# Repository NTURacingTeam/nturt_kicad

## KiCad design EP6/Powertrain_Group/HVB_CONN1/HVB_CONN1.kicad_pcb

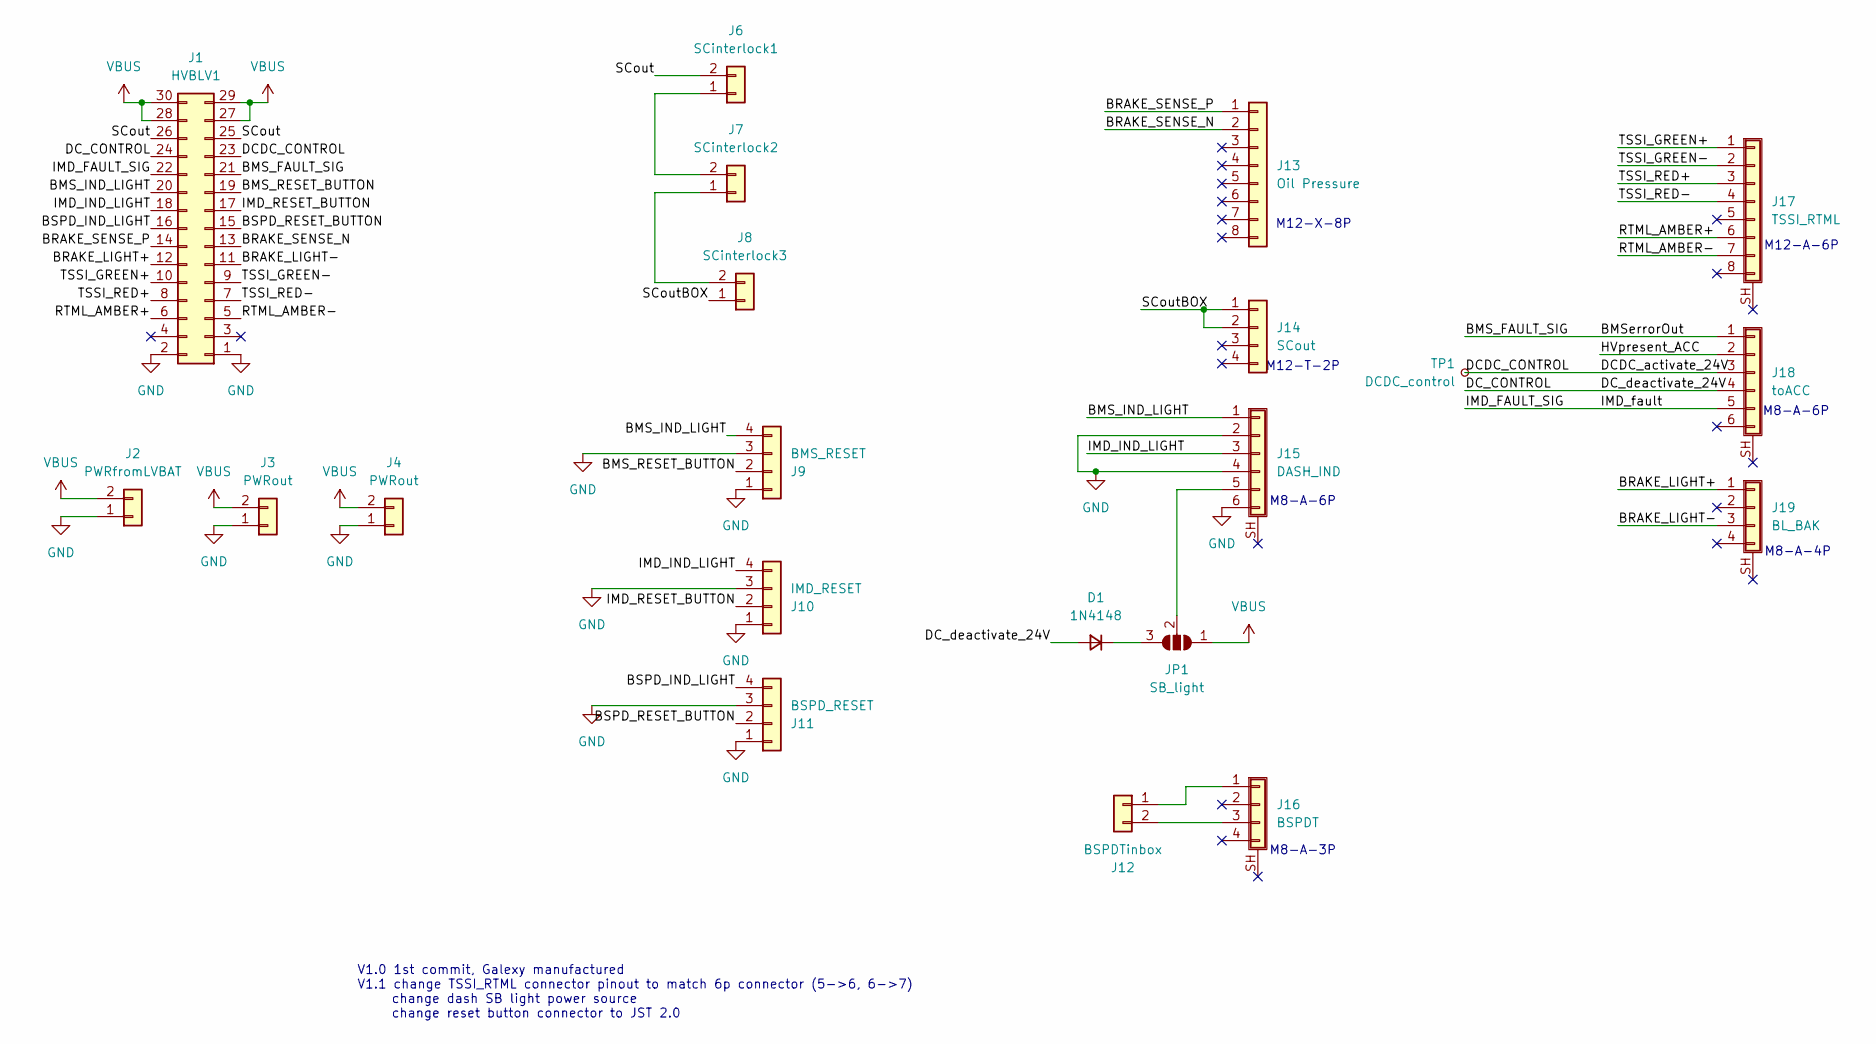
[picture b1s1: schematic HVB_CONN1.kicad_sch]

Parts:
D1: 1N4148; D_SOD-323_HandSoldering
J1: HVBLV1; IDC-Header_2x15_P2.54mm_Vertical_SMD
J2: PWRfromLVBAT; JST_VH_B2P-VH_1x02_P3.96mm_Vertical
J3, J4: PWRout; JST_VH_B2P-VH_1x02_P3.96mm_Vertical
J6: SCinterlock1; JST_VH_B2P-VH_1x02_P3.96mm_Vertical
J7: SCinterlock2; JST_VH_B2P-VH_1x02_P3.96mm_Vertical
J8: SCinterlock3; JST_VH_B2P-VH_1x02_P3.96mm_Vertical
J9: BMS_RESET; JST_PH_B4B-PH-K_1x04_P2.00mm_Vertical
J10: IMD_RESET; JST_PH_B4B-PH-K_1x04_P2.00mm_Vertical
J11: BSPD_RESET; JST_PH_B4B-PH-K_1x04_P2.00mm_Vertical
J12: BSPDTinbox; JST_PH_B2B-PH-K_1x02_P2.00mm_Vertical
J13: Oil Pressure; NianYeong-M12-X-F4P
J14: SCout; NianYeong-M12-T-M4P
J15: DASH_IND; WP-06F3-09-11
J16: BSPDT; WP-03F3-09-11
J17: TSSI_RTML; NianYeong-M12-A-F8P-Shield
J18: toACC; WP-06F3-09-11
J19: BL_BAK; WP-04F3-26-11
JP1: SB_light; SolderJumper-3_P1.3mm_Open_RoundedPad1.0x1.5mm
TP1: DCDC_control; TestPoint_Pad_D1.0mm

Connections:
/BMS_FAULT_SIG: J1.21, J18.1
/BMS_IND_LIGHT: J1.20, J9.4, J15.1
/BMS_RESET_BUTTON: J1.19, J9.2
/BRAKE_LIGHT+: J1.12, J19.1
/BRAKE_LIGHT-: J1.11, J19.3
/BRAKE_SENSE_N: J1.13, J13.2
/BRAKE_SENSE_P: J1.14, J13.1
/BSPD_IND_LIGHT: J1.16, J11.4
/BSPD_RESET_BUTTON: J1.15, J11.2
/DCDC_CONTROL: J1.23, J18.3, TP1.1
/DC_CONTROL: D1.2 (A), J1.24, J18.4
/HVpresent_ACC: J18.2
/IMD_FAULT_SIG: J1.22, J18.5
/IMD_IND_LIGHT: J1.18, J10.4, J15.3
/IMD_RESET_BUTTON: J1.17, J10.2
/RTML_AMBER+: J1.6, J17.6
/RTML_AMBER-: J1.5, J17.7
/SCout: J1.25, J1.26, J6.2
/SCoutBOX: J8.1, J14.1, J14.2
/TSSI_GREEN+: J1.10, J17.1
/TSSI_GREEN-: J1.9, J17.2
/TSSI_RED+: J1.8, J17.3
/TSSI_RED-: J1.7, J17.4
GND: J1.1, J1.2, J2.1, J3.1, J4.1, J9.1, J9.3, J10.1, J10.3, J11.1, J11.3, J15.2, J15.4, J15.6
unnamed: D1.1 (K), JP1.3 (B)
unnamed: J6.1, J7.2
unnamed: J7.1, J8.2
unnamed: J12.1, J16.1
unnamed: J12.2, J16.3
unnamed: J15.5, JP1.2 (C)
VBUS: J1.27, J1.28, J1.29, J1.30, J2.2, J3.2, J4.2, JP1.1 (A)

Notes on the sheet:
M12-T-2P
M8-A-4P
M12-X-8P
M8-A-3P
M12-A-6P
V1.0 1st commit, Galexy manufactured V1.1 change TSSI_RTML connector pinout to match 6p connector (5->6, 6->7) change dash SB light power source change reset button connector to JST 2.0
M8-A-6P

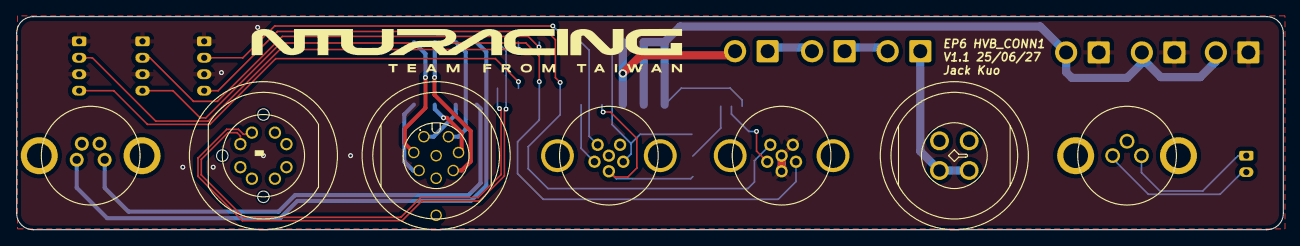
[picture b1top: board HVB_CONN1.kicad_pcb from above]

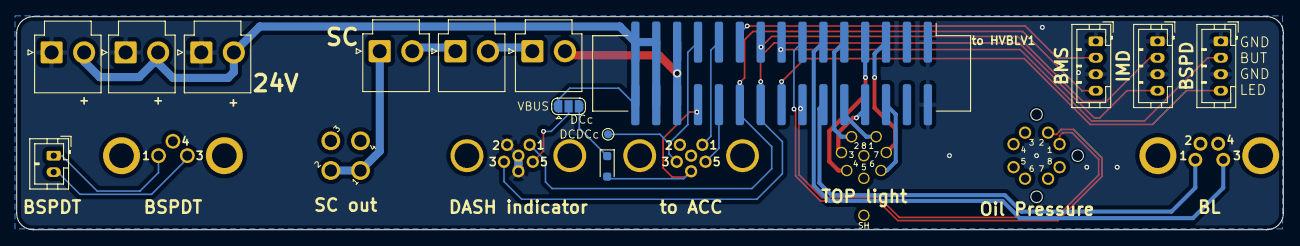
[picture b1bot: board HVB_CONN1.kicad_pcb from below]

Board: 2 copper layers, 154.0 x 25.9 mm, 21 parts (14 on the bottom side), 30 nets.

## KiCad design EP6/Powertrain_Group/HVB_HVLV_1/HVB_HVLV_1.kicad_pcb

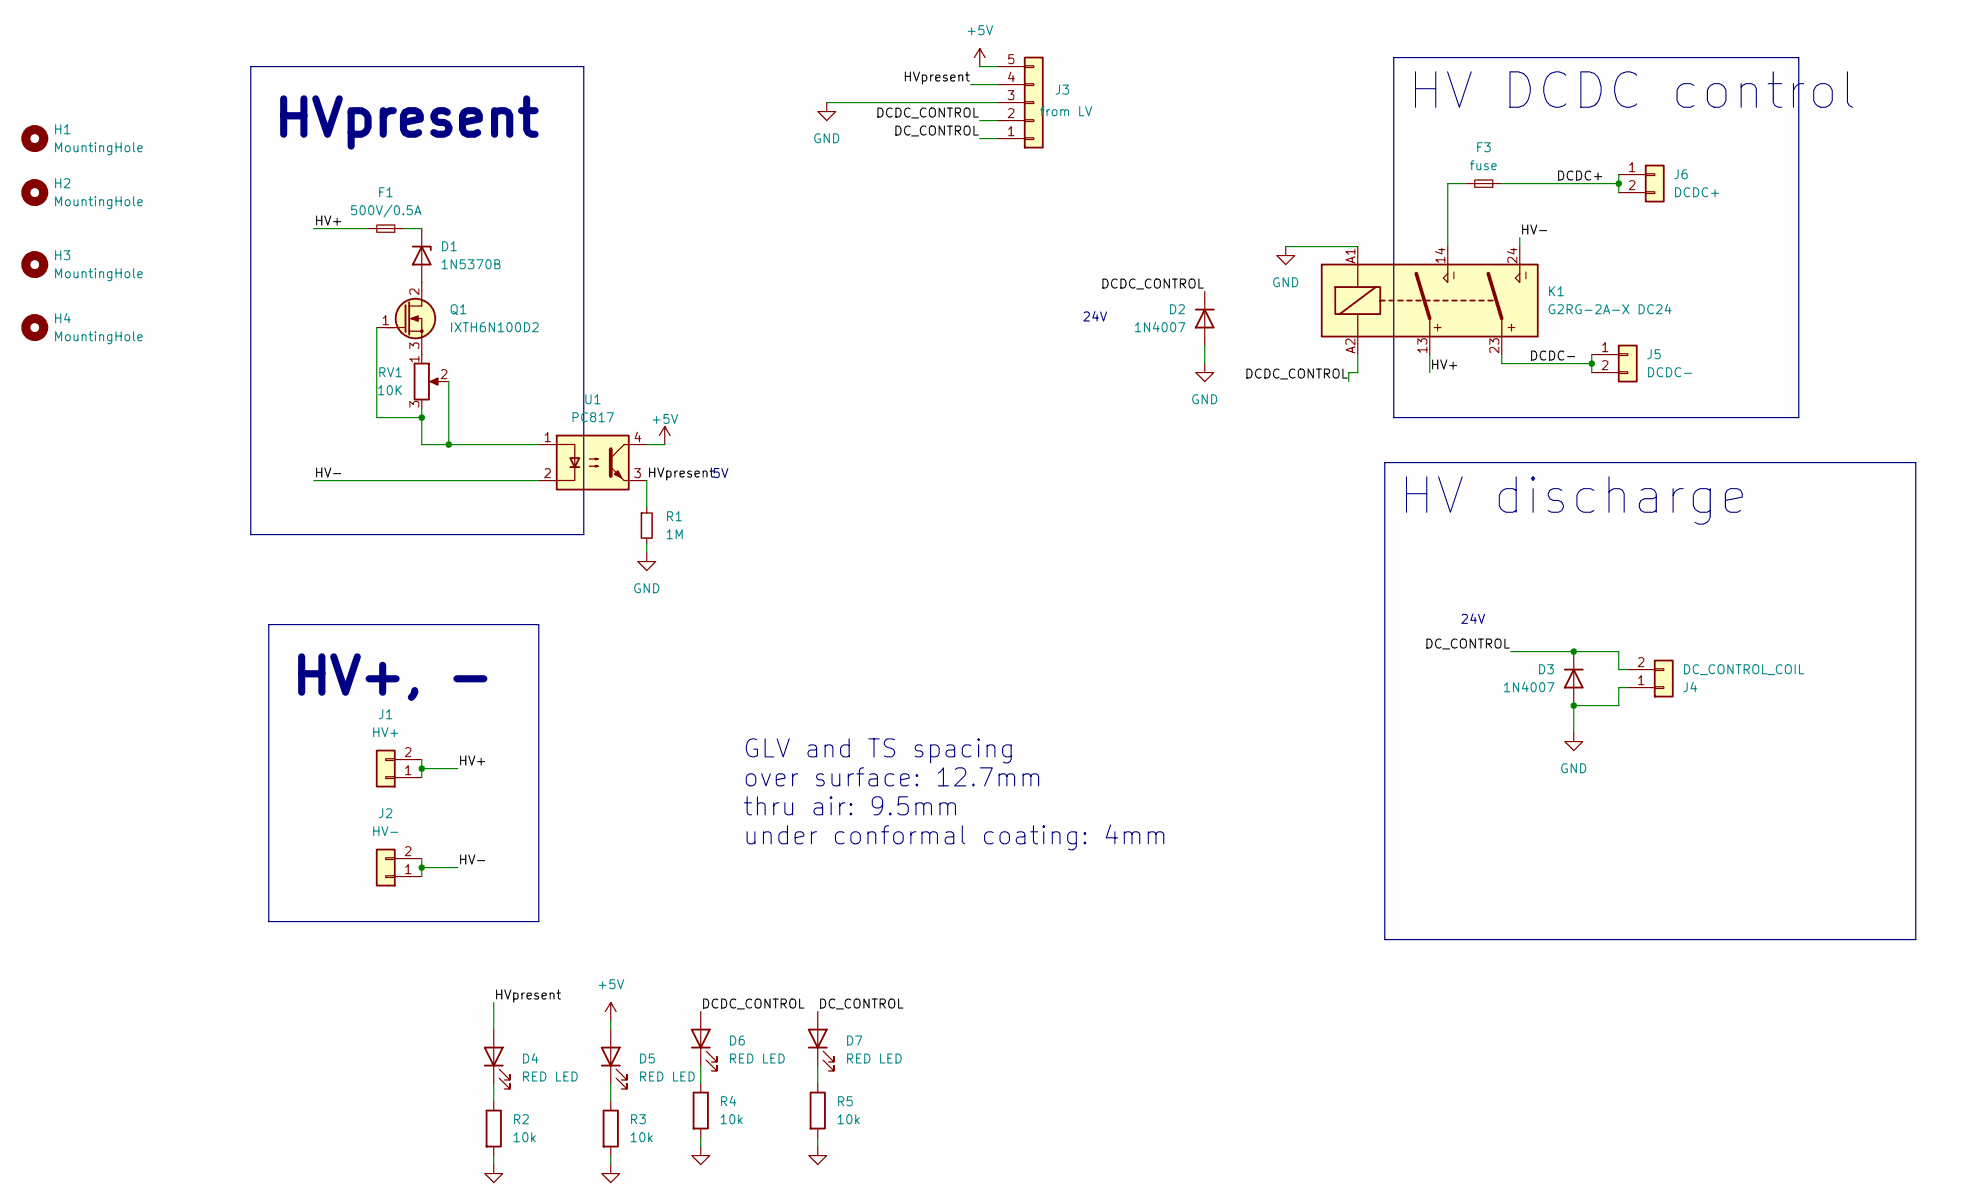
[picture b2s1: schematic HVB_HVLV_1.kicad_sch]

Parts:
D1: 1N5370B; D_DO-201_P15.24mm_Horizontal
D2, D3: 1N4007; D_DO-41_SOD81_P10.16mm_Horizontal
D4, D5, D6, D7: RED LED; LED_0603_1608Metric
F1: 500V/0.5A; 65600001009; Rating W
F3: fuse; 65600001009; Rating W
H1, H2, H3, H4: MountingHole; MountingHole_3.2mm_M3
J1: HV+; HRS_DF33C-2P-3.3DSA
J2: HV-; HRS_DF33C-2P-3.3DSA
J3: from LV; JST_PH_B5B-PH-K_1x05_P2.00mm_Vertical
J4: DC_CONTROL_COIL; JST_VH_B2P-VH_1x02_P3.96mm_Vertical
J5: DCDC-; HRS_DF33C-2P-3.3DSA
J6: DCDC+; HRS_DF33C-2P-3.3DSA
K1: G2RG-2A-X DC24; Relay_DPST_Omron_G2RL-2A
Q1: IXTH6N100D2; TO-247-3_Vertical_GDS
R1: 1M; R_0603_1608Metric
R2, R3, R4, R5: 10k; R_0603_1608Metric
RV1: 10K; Throughhole Potentiometer 3296W
U1: PC817; DIP-4_W7.62mm

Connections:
+5V: D5.2 (A), J3.5, U1.4
/DCDC+: F3.1, J6.1, J6.2
/DCDC-: J5.1, J5.2, K1.23
/DCDC_CONTROL: D2.1 (K), D6.2 (A), J3.2, K1.A2
/DC_CONTROL: D3.1 (K), D7.2 (A), J3.1, J4.2
/HV+: F1.2, J1.1, J1.2, K1.13
/HV-: J2.1, J2.2, K1.24, U1.2
/HVpresent: D4.2 (A), J3.4, R1.1, U1.3
GND: D2.2 (A), D3.2 (A), J3.3, J4.1, K1.A1, R1.2, R2.2, R3.2, R4.2, R5.2
unnamed: D1.2 (A), Q1.2 (D)
unnamed: D1.1 (K), F1.1
unnamed: D4.1 (K), R2.1
unnamed: D5.1 (K), R3.1
unnamed: D6.1 (K), R4.1
unnamed: D7.1 (K), R5.1
unnamed: F3.2, K1.14
unnamed: Q1.1 (G), RV1.2, RV1.3, U1.1
unnamed: Q1.3 (S), RV1.1

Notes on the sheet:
HVpresent
HV DCDC control
24V
HV discharge
HV+, -
GLV and TS spacing over surface: 12.7mm thru air: 9.5mm under conformal coating: 4mm

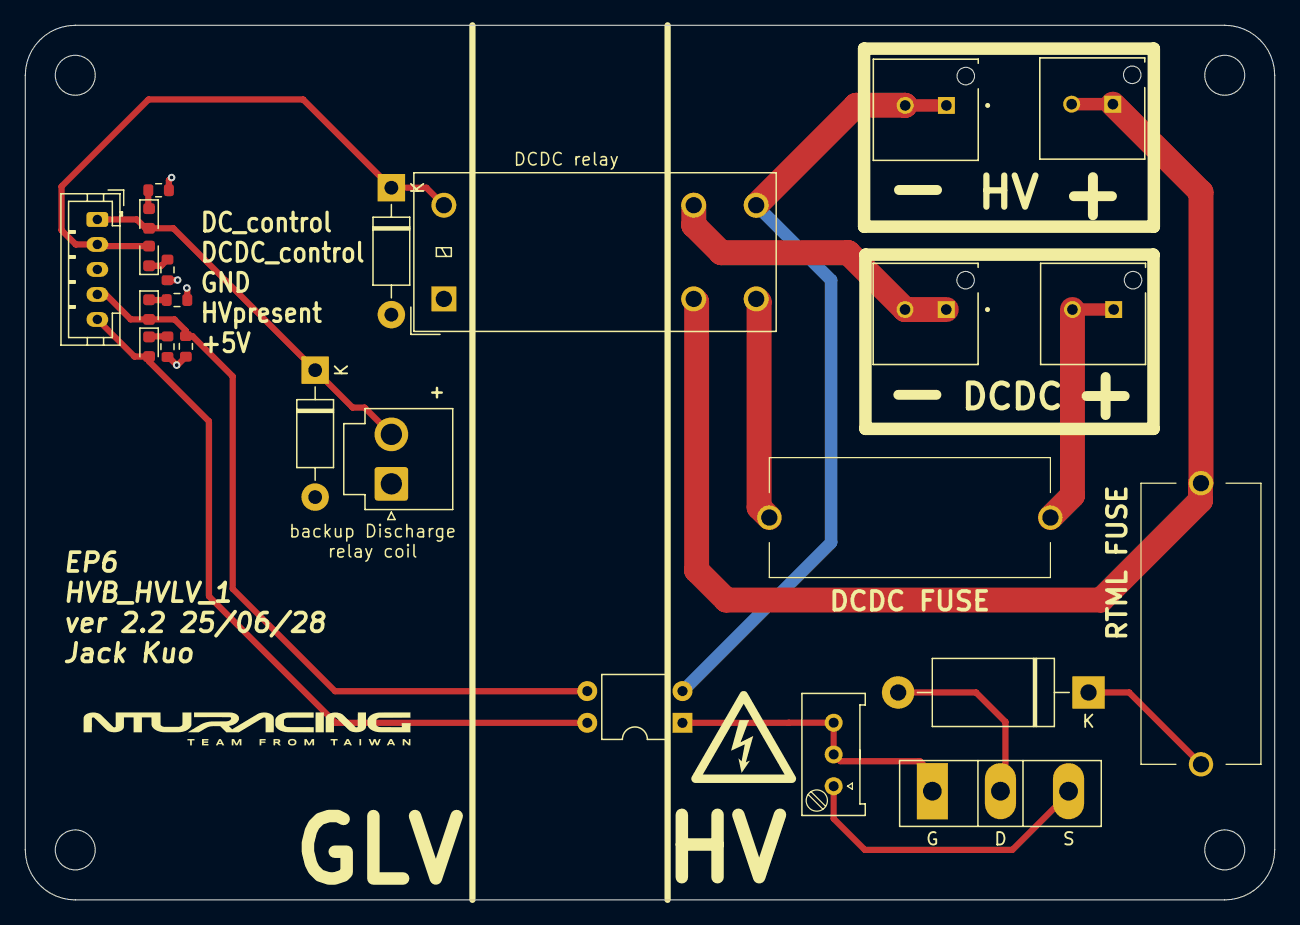
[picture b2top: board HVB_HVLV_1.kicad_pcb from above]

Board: 2 copper layers, 100.0 x 70.0 mm, 28 parts (0 on the bottom side), 18 nets.

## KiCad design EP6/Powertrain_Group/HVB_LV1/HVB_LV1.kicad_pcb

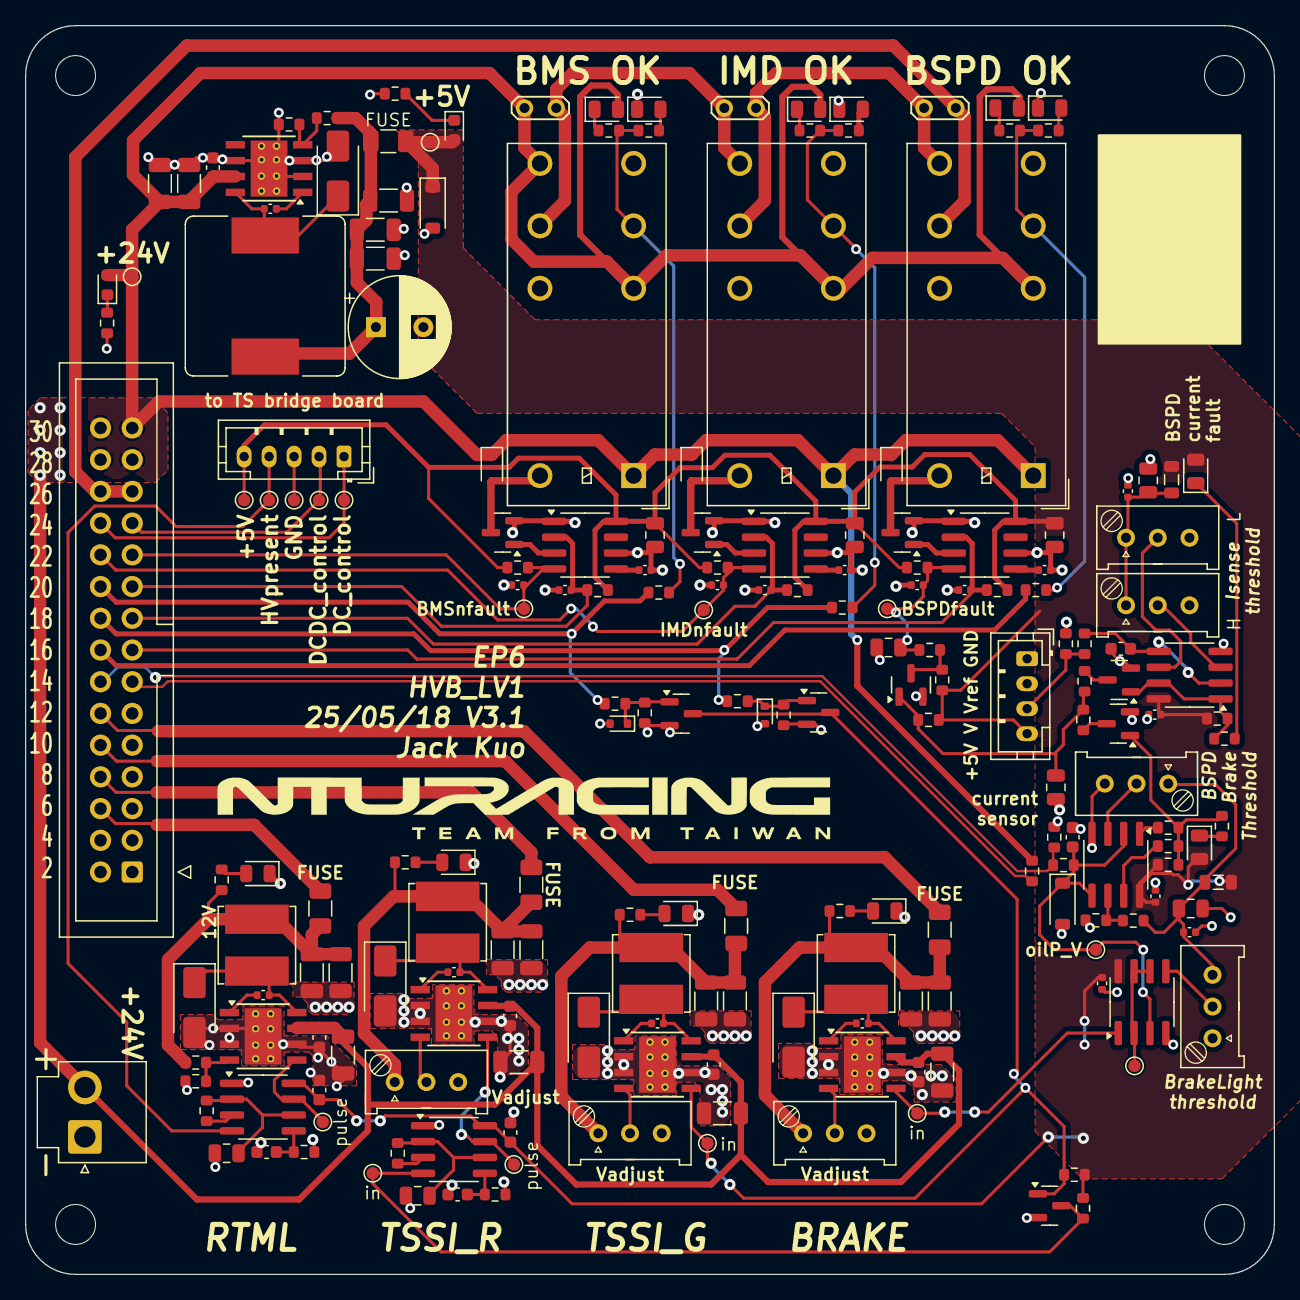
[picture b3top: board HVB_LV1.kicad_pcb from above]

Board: 2 copper layers, 100.0 x 100.0 mm, 208 parts (0 on the bottom side), 102 nets.

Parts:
C1, C5, C9, C14, C17, C19, C52, C55, C57: 10u; C_0805_2012Metric
C2, C4, C6, C8, C10, C12, C13, C15, C16, C20, C21: 100n; C_0402_1005Metric
C3, C7, C11, C22, C30, C35, C40, C45: 10n; C_0402_1005Metric
C18, C56: 10u; C_0603_1608Metric
C23, C24, C31, C36, C41, C46: 10u 35V; C_1206_3216Metric
C25, C32, C37, C42, C47, C50, C51, C53, C54: 100n; C_0603_1608Metric
C26, C27, C28, C33, C34, C38, C39, C43, C44, C48, C49: 22u 25V; C_1206_3216Metric
C29: 330u 25V; CP_Radial_D8.0mm_P3.80mm
D1, D4, D7: 4148; D_SOD-323
D2, D5, D8, D10, D12: GREEN LED; LED_0805_2012Metric
D3, D6, D9: RED LED; LED_0805_2012Metric
D11, D16: 5.6V (C19077402); D_SOD-123
D13, D15: WHITE LED; LED_0603_1608Metric
D14, D19, D20, D21, D22: SS54; D_SMA
D17, D18: BZX584C5V6; D_SOD-523
D23, D24, D25, D26: YELLOW LED; LED_0805_2012Metric
F1: 2A; Fuse_1206_3216Metric
F2, F3, F4, F5: FUSE; Fuse_1206_3216Metric
FB1, FB2: GZ1608D601TF; L_0805_2012Metric
H1, H2, H3, H4: MountingHole; MountingHole_3.2mm_M3
J1: toTS; JST_PH_B5B-PH-K_1x05_P2.00mm_Vertical
J2: energy meter; JST_VH_B2P-VH-B_1x02_P3.96mm_Vertical
J3: toConnectorBoard; IDC-Header_2x15_P2.54mm_Vertical
J4: I_Sen; JST_PH_B4B-PH-K_1x04_P2.00mm_Vertical
JP2, JP3, JP4: test; TestPoint_2Pads_Pitch2.54mm_Drill0.8mm
L1: 22uH 4.95A (SMDRI129-220MT); L_Bourns_SRR1260
L2, L3, L4, L5: 47u 1.6A (SRN6045TA-470M); L_Bourns_SRN6045TA
Q1, Q2, Q3, Q4, Q5, Q6, Q7, Q8, Q9: 2N7002; SOT-23
R1, R2, R5, R6, R7, R10, R11, R12, R15, R21, R25, R35, R37, R38, R39, R41, R44, R46, R48, R50, R51, R52, R53: 10k; R_0603_1608Metric
R3, R8, R13, R18, R19, R27, R29: 0R; R_0603_1608Metric
R4, R9, R14, R23, R31, R32, R40, R42: 100k; R_0603_1608Metric
R16, R17: 10R; R_0603_1608Metric
R20: 150R; R_0603_1608Metric
R22, R30: 4k7; R_0603_1608Metric
R24, R49: 1k; R_0603_1608Metric
R26: 20k; R_0603_1608Metric
R28: 100R; R_0603_1608Metric
R33, R34: 47k; R_0603_1608Metric
R36: 15k; R_0603_1608Metric
R43: 91k; R_0603_1608Metric
R45, R47: 43k; R_0603_1608Metric
RL1, RL2, RL3: G2RL-24-DC24; Relay_DPDT_Omron_G2RL-2
RV1, RV2, RV3, RV4, RV5, RV6, RV7: 10k; Throughhole Potentiometer 3296W
TP1: +5V; TestPoint_Pad_D1.0mm
TP2: HVpresent; TestPoint_Pad_D1.0mm
TP3: GND; TestPoint_Pad_D1.0mm
TP4: DCDC_control; TestPoint_Pad_D1.0mm
TP5: DC_control; TestPoint_Pad_D1.0mm
TP6: BMSfault; TestPoint_Pad_D1.0mm
TP7: IMDfault; TestPoint_Pad_D1.0mm
TP8: BSPDnfault; TestPoint_Pad_D1.0mm
TP9: BrakeThreshold; TestPoint_Pad_D1.0mm
TP10: oilP_Vout; TestPoint_Pad_D1.0mm
TP11: Vbus; TestPoint_Pad_D1.0mm
TP12: 5V; TestPoint_Pad_D1.0mm
TP13: RTML; TestPoint_Pad_D1.0mm
TP14: TSSI RED RAW; TestPoint_Pad_D1.0mm
TP15: TSSI Red; TestPoint_Pad_D1.0mm
TP16: TSSI Green; TestPoint_Pad_D1.0mm
TP17: BrakeLight; TestPoint_Pad_D1.0mm
U1, U2, U3, U12, U13: NE555D; SOIC-8_3.9x4.9mm_P1.27mm
U4: LM358; SOIC-8_3.9x4.9mm_P1.27mm
U5, U6: LM393; SOIC-8_3.9x4.9mm_P1.27mm
U7, U8, U9, U10, U11: TPS5430DDAR; TI_SO-PowerPAD-8_ThermalVias

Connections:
+5V: C1.1, C5.1, C9.1, C15.1, C20.1, C21.1, C50.1, C53.1, D10.2 (A), D12.2 (A), D15.2 (A), D16.1 (K), F1.2, FB1.2, FB2.2, J1.5, J4.4, R1.1, R4.1, R6.1, R9.1, R11.1, R14.1, R21.1, R23.1, R25.1, R31.1, R37.1, R38.1, TP1.1, TP12.1, U1.8 (VCC), U2.8 (VCC), U3.8 (VCC), U4.8 (V+), U5.8 (V+), U6.8 (V+), U12.8 (VCC), U13.8 (VCC)
+5VA: C13.1, C14.1, FB1.1, RV3.1, RV4.1
/BMS_IND_LIGHT: J3.20, R3.2, R39.1
/BMS_RESET_BUTTON: C2.1, J3.19, R1.2, U1.2 (TR)
/BMS_nFAULT_SIG_RAW: C4.1, J3.21, R4.2, TP6.1, U1.4 (R)
/BRAKE_LIGHT+: F5.2, J3.12
/BRAKE_SENSE_N: J3.13, R16.1
/BRAKE_SENSE_P: J3.14, R17.1, R20.1
/BSPD/5VA2: C16.1, C17.1, FB2.1, R26.1, RV1.3, RV2.1
/BSPD/BSPDfault: C57.1, Q5.1 (G), R19.2, R25.2, R29.2
/BSPD/DCbusCurrentAbsent: Q6.1 (G), R30.2, R31.2, U6.1, U6.7
/BSPD/DCbusCurrentNotGood: Q6.3 (D), R29.1
/BSPD/OilPsenserPresent: R27.1, U5.7
/BSPD/brakeLightOn: TP17.1, U4.1, U11.5 (EN)
/BSPD/brakeNotInSafeArea: Q4.3 (D), R19.1
/BSPD/nohardBrake: R18.1, U5.1
/BSPD_IND_LIGHT: J3.16, R13.2
/BSPD_RESET_BUTTON: C10.1, J3.15, R11.2, U3.2 (TR)
/BSPD_nFAULT_SIG: C12.1, C19.1, R14.2, R24.1, TP8.1, U3.4 (R)
/BrightLight/RTML amber/12V_buck: C33.1, C34.1, F2.1, L2.1, R43.1, R50.2
/BrightLight/RTML amber/12V_buck_FB: R43.2, R44.1, U8.4 (VSENSE)
/BrightLight/RTML amber/12V_buck_sw: C30.2, D19.1 (K), L2.2, U8.8 (PH)
/BrightLight/RTML amber/enable: TP13.1, U8.5 (EN), U12.7 (DIS)
/BrightLight/TSSI green/buck_FB: RV6.2, U10.4 (VSENSE)
/BrightLight/TSSI green/buck_out: C43.1, C44.1, F4.1, L4.1, R52.2, RV6.1
/BrightLight/TSSI green/buck_sw: C40.2, D21.1 (K), L4.2, U10.8 (PH)
/BrightLight/TSSI green/enable: Q7.1 (G), Q8.3 (D), Q9.3 (D), R38.2, TP16.1, U10.5 (EN)
/BrightLight/TSSI red pulse/OpenDrain_pulse_out: TP15.1, U9.5 (EN), U13.7 (DIS)
/BrightLight/TSSI red pulse/enable: Q7.3 (D), R37.2, TP14.1, U13.4 (R)
/BrightLight/TSSI red/buck_FB: RV5.2, U9.4 (VSENSE)
/BrightLight/TSSI red/buck_out: C38.1, C39.1, F3.1, L3.1, R51.2, RV5.1
/BrightLight/TSSI red/buck_sw: C35.2, D20.1 (K), L3.2, U9.8 (PH)
/BrightLight/brakelight/buck_FB: RV7.2, U11.4 (VSENSE)
/BrightLight/brakelight/buck_out: C48.1, C49.1, F5.1, L5.1, R53.2, RV7.1
/BrightLight/brakelight/buck_sw: C45.2, D22.1 (K), L5.2, U11.8 (PH)
/CURRENT_MEASSURED: J4.3, R32.1, R49.1
/DCDC_CONTROL: J1.2, J3.23, TP4.1
/DC_CONTROL: J1.1, J3.24, TP5.1
/HVpresent: J1.4, TP2.1, U12.4 (R)
/IMD_IND_LIGHT: J3.18, R8.2, R41.1
/IMD_RESET_BUTTON: C6.1, J3.17, R6.2, U2.2 (TR)
/IMD_nFAULT_SIG_RAW: C8.1, J3.22, R9.2, TP7.1, U2.4 (R)
/Latch_BMS/SC_OUT: JP2.2 (B), JP3.1 (A), RL1.21, RL2.24
/Latch_BSPD/SC_IN: JP3.2 (B), JP4.1 (A), RL2.21, RL3.24
/Power/5V_buck: C26.1, C27.1, C28.1, C29.1, F1.1, L1.2, R34.1
/Power/5V_buck_FB: R34.2, R36.1, U7.4 (VSENSE)
/Power/5V_buck_sw: C22.2, D14.1 (K), L1.1, U7.8 (PH)
/RTML_AMBER+: F2.2, J3.6
/SCout: J3.25, J3.26, JP4.2 (B), RL3.21
/TSSI_GREEN+: F4.2, J3.10
/TSSI_RED+: F3.2, J3.8
GND: C1.2, C2.2, C3.2, C4.2, C5.2, C6.2, C7.2, C8.2, C9.2, C10.2, C11.2, C12.2, C13.2, C14.2, C15.2, C16.2, C17.2, C18.2, C19.2, C20.2, C21.2, C23.2, C24.2, C25.1, C26.2, C27.2, C28.2, C29.2, C31.2, C32.1, C33.2, C34.2, C36.2, C37.1, C38.2, C39.2, C41.2, C42.1, C43.2, C44.2, C46.2, C47.1, C48.2, C49.2, C50.2, C51.2, C52.2, C53.2, C54.2, C55.2, C56.2, C57.2, D3.1 (K), D6.1 (K), D9.1 (K), D11.2 (A), D14.2 (A), D16.2 (A), D17.2 (A), D18.2 (A), D19.2 (A), D20.2 (A), D21.2 (A), D22.2 (A), D23.1 (K), D24.1 (K), D25.1 (K), D26.1 (K), J1.3, J2.1, J3.1, J3.2, J3.5, J3.7, J3.9, J3.11, J4.1, Q1.2 (S), Q2.2 (S), Q3.2 (S), Q4.2 (S), Q5.2 (S), Q6.2 (S), Q7.2 (S), Q8.2 (S), Q9.2 (S), R20.2, R28.2, R32.2, R33.2, R35.2, R36.2, R40.1, R42.1, R44.2, R46.1, R48.1, RL1.14, RL2.14, RL3.14, RV1.1, RV2.3, RV3.3, RV4.3, RV5.3, RV6.3, RV7.3, TP3.1, U1.1 (GND), U1.6 (THR), U2.1 (GND), U2.6 (THR), U3.1 (GND), U3.6 (THR), U4.4 (V-), U5.4 (V-), U6.4 (V-), U7.2 (NC), U7.3 (NC), U7.6 (GND), U7.9 (GNDPAD), U8.2 (NC), U8.3 (NC), U8.6 (GND), U8.9 (GNDPAD), U9.2 (NC), U9.3 (NC), U9.6 (GND), U9.9 (GNDPAD), U10.2 (NC), U10.3 (NC), U10.6 (GND), U10.9 (GNDPAD), U11.2 (NC), U11.3 (NC), U11.6 (GND), U11.9 (GNDPAD), U12.1 (GND), U13.1 (GND)
unnamed: D1.2 (A), Q1.3 (D), RL1.A2
unnamed: D2.1 (K), R2.1
unnamed: D3.2 (A), R5.1
unnamed: D4.2 (A), Q2.3 (D), RL2.A2
unnamed: D5.1 (K), R7.1
unnamed: D6.2 (A), R10.1
unnamed: D7.2 (A), Q3.3 (D), RL3.A2
unnamed: D8.1 (K), R12.1
unnamed: D9.2 (A), R15.1
unnamed: D10.1 (K), R22.1
unnamed: C18.1, D11.1 (K), R17.2, TP10.1, U4.3 (+), U5.2 (-), U5.5 (+)
unnamed: D12.1 (K), R30.1
unnamed: D13.1 (K), R33.1
unnamed: D15.1 (K), R35.1
unnamed: D17.1 (K), Q8.1 (G), R39.2, R40.2
unnamed: D18.1 (K), Q9.1 (G), R41.2, R42.2
unnamed: D23.2 (A), R50.1
unnamed: D24.2 (A), R51.1
unnamed: D25.2 (A), R52.1
unnamed: D26.2 (A), R53.1
unnamed: Q1.1 (G), U1.3 (Q)
unnamed: Q2.1 (G), U2.3 (Q)
unnamed: Q3.1 (G), U3.3 (Q)
unnamed: Q4.1 (G), R18.2, R22.2, R23.2, R27.2
unnamed: Q5.3 (D), R21.2, R24.2
unnamed: R2.2, R3.1, R5.2, RL1.11
unnamed: R7.2, R8.1, R10.2, RL2.11
unnamed: R12.2, R13.1, R15.2, RL3.11
unnamed: C3.1, U1.5 (CV)
unnamed: C7.1, U2.5 (CV)
unnamed: C11.1, U3.5 (CV)
unnamed: TP9.1, U4.2 (-), U4.6 (-), U4.7
unnamed: RV1.2, U4.5 (+)
unnamed: RV2.2, U5.3 (+)
unnamed: R26.2, R28.1, U5.6 (-)
unnamed: RV3.2, U6.3 (+)
unnamed: C56.1, R49.2, U6.2 (-), U6.5 (+)
unnamed: RV4.2, U6.6 (-)
unnamed: C22.1, U7.1 (BOOT)
unnamed: C30.1, U8.1 (BOOT)
unnamed: C35.1, U9.1 (BOOT)
unnamed: C40.1, U10.1 (BOOT)
unnamed: C45.1, U11.1 (BOOT)
unnamed: C51.1, R46.2, U12.5 (CV)
unnamed: R45.2, U12.3 (Q)
unnamed: C52.1, R45.1, U12.2 (TR), U12.6 (THR)
unnamed: C54.1, R48.2, U13.5 (CV)
unnamed: R47.2, U13.3 (Q)
unnamed: C55.1, R47.1, U13.2 (TR), U13.6 (THR)
VBUS: C23.1, C24.1, C25.2, C31.1, C32.2, C36.1, C37.2, C41.1, C42.2, C46.1, C47.2, D1.1 (K), D2.2 (A), D4.1 (K), D5.2 (A), D7.1 (K), D8.2 (A), D13.2 (A), J2.2, J3.27, J3.28, J3.29, J3.30, JP2.1 (A), R16.2, RL1.12, RL1.24, RL1.A1, RL2.12, RL2.A1, RL3.12, RL3.A1, TP11.1, U7.7 (VIN), U8.7 (VIN), U9.7 (VIN), U10.7 (VIN), U11.7 (VIN)

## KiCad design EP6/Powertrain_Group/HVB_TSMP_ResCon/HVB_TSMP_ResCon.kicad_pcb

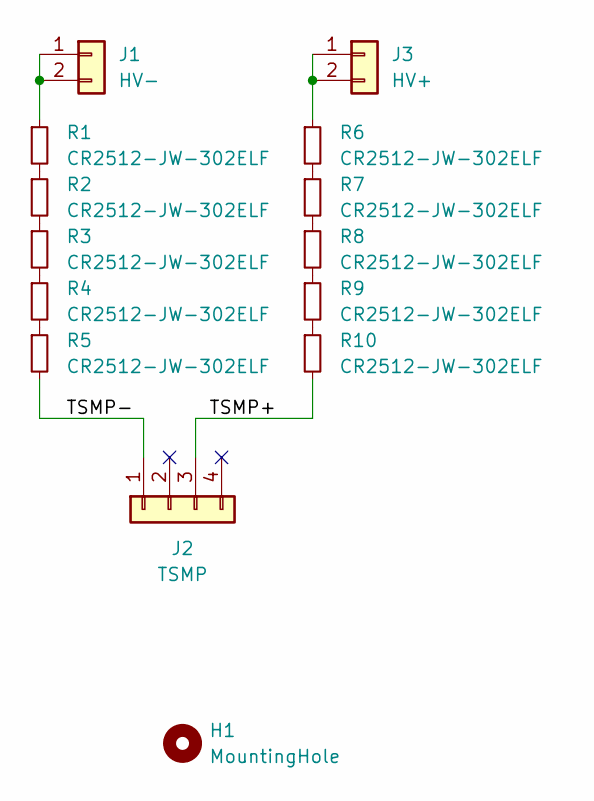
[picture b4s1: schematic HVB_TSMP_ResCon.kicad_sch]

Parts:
H1: MountingHole; MountingHole_3.2mm_M3
J1: HV-; HRS_DF33C-2P-3.3DSA
J2: TSMP; NianYeong-M12-S-M4P
J3: HV+; HRS_DF33C-2P-3.3DSA
R1, R2, R3, R4, R5, R6, R7, R8, R9, R10: CR2512-JW-302ELF; R_2512_6332Metric

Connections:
/TSMP+: J2.3, R10.2
/TSMP-: J2.1, R5.2
unnamed: J1.1, J1.2, R1.1
unnamed: J3.1, J3.2, R6.1
unnamed: R1.2, R2.1
unnamed: R2.2, R3.1
unnamed: R3.2, R4.1
unnamed: R4.2, R5.1
unnamed: R6.2, R7.1
unnamed: R7.2, R8.1
unnamed: R8.2, R9.1
unnamed: R9.2, R10.1

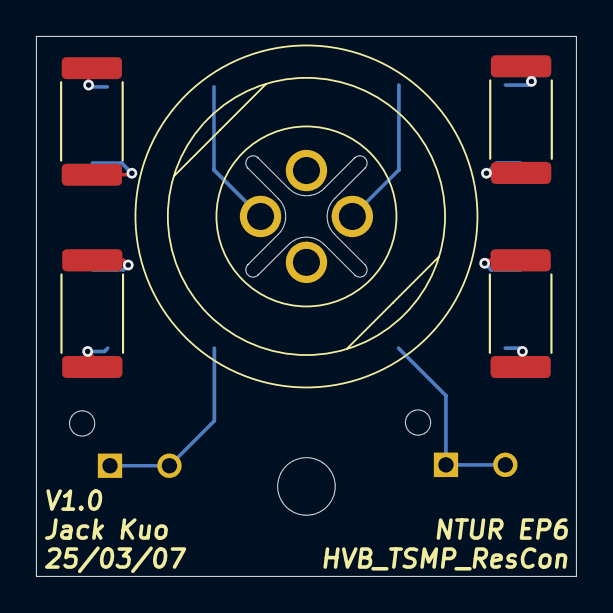
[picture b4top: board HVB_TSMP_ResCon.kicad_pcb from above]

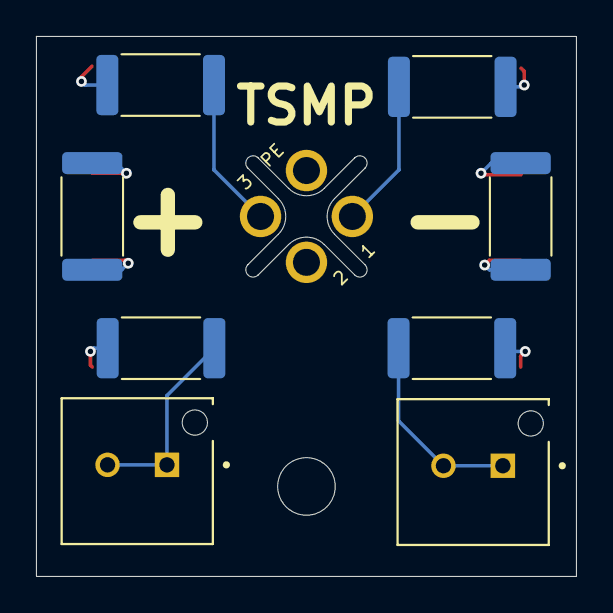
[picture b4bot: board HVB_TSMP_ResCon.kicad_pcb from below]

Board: 2 copper layers, 30.0 x 30.0 mm, 14 parts (8 on the bottom side), 12 nets.

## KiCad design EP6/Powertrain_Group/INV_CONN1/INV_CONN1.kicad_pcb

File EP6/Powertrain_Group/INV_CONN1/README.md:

# INV_CONN1 KiCad Project

## Project Overview
This repository contains the KiCad project for the **INV_CONN1** design, developed as part of the **Powertrain Group**.
It has 2 L-coded for 24V+CAN, 1 for SCio, 1 for debug (compatable with TI JTAG and STM32 STDC14)

## Author
- **Name:** [Jack Kuo](https://github.com/chemmy-jack)
- **Team:** NTU Racing Team Powertrain Group

## Revision History

| Version | Date       | Author       | Description                  |
|---------|------------|--------------|------------------------------|
| 1.0     | 2025-03-10 | [Jack Kuo](https://github.com/chemmy-jack)  | Initial project creation.    |
| 1.1     | 2025-04-27 | [Jack Kuo](https://github.com/chemmy-jack)  |  fix M12 L-coded hole too small mistake.  add fillet to board cut. add gournd under CAN trace for correct impedence match. sch not changed. |
| 1.2     | 2025-05-04 | [Jack Kuo](https://github.com/chemmy-jack)  |  change a L-coded with SC T-coded for better hieght match (because L-coded is too short, the new form allows the two L-coded be easily cut out) |

## To-Do List

## License
<!-- This project is licensed under [Your License]. See the LICENSE file for details. -->
none

## Contact
For questions or contributions, please contact [ntu.racing@gmail.com].

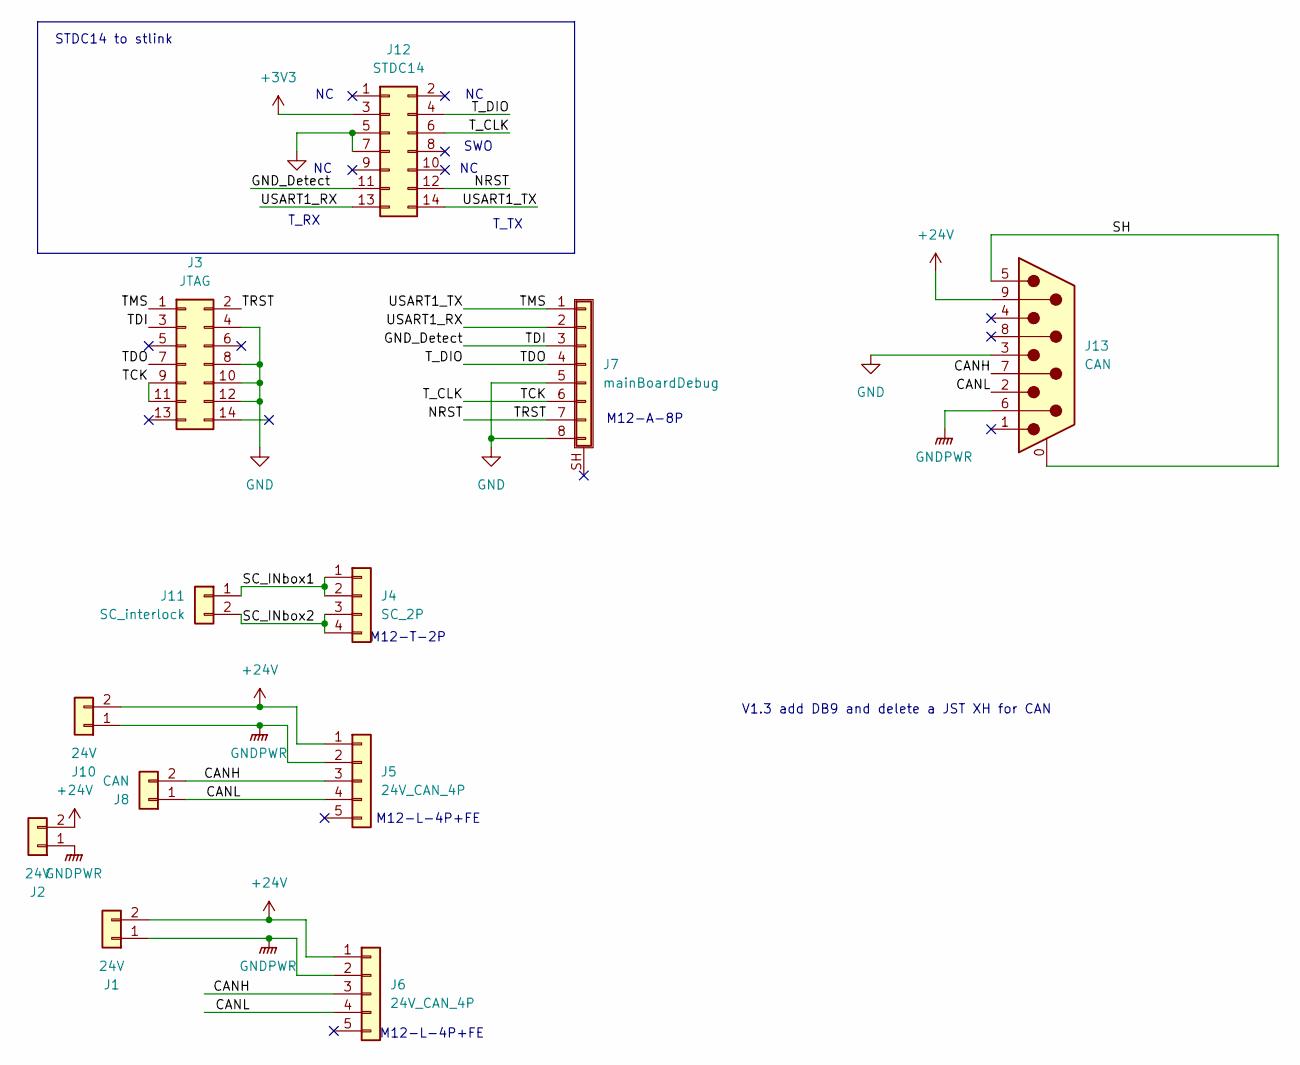
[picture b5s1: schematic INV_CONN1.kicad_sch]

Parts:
J1, J2, J10: 24V; JST_VH_B2P-VH_1x02_P3.96mm_Vertical
J3: JTAG; IDC-Header_2x07_P2.54mm_Vertical
J4: SC_2P; NianYeong-M12-T-M4P
J5, J6: 24V_CAN_4P; NianYeong-M12-L-F5P
J7: mainBoardDebug; NianYeong-M12-A-F8P-Shield
J8: CAN; JST_XH_B2B-XH-A_1x02_P2.50mm_Vertical
J11: SC_interlock; JST_VH_B2P-VH_1x02_P3.96mm_Vertical
J12: STDC14; box_header_14P_pitch127
J13: CAN; DSUB-9_Female_Vertical_P2.77x2.84mm_MountingHoles

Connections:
+3V3: J12.3
+24V: J1.2, J2.2, J5.1, J6.1, J10.2, J13.9
/CANH: J5.3, J6.3, J8.2, J13.7
/CANL: J5.4, J6.4, J8.1, J13.2
/GND_Detect: J3.3, J7.3, J12.11
/NRST: J3.2, J7.7, J12.12
/SC_INbox1: J4.1, J4.2, J11.1
/SC_INbox2: J4.3, J4.4, J11.2
/SH: J13.0 (PAD), J13.5
/TCK: J3.9, J3.11, J7.6, J12.6
/TDO: J3.7, J7.4, J12.4
/TMS: J3.1, J7.1, J12.14
/USART1_RX: J7.2, J12.13
GND: J3.4, J3.8, J3.10, J3.12, J7.5, J7.8, J12.5, J12.7, J13.3
GNDPWR: J1.1, J2.1, J5.2, J6.2, J10.1, J13.6

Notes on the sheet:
STDC14 to stlink
SWO
M12-T-2P
T_RX
M12-L-4P+FE
V1.3 add DB9 and delete a JST XH for CAN
M12-A-8P
T_TX

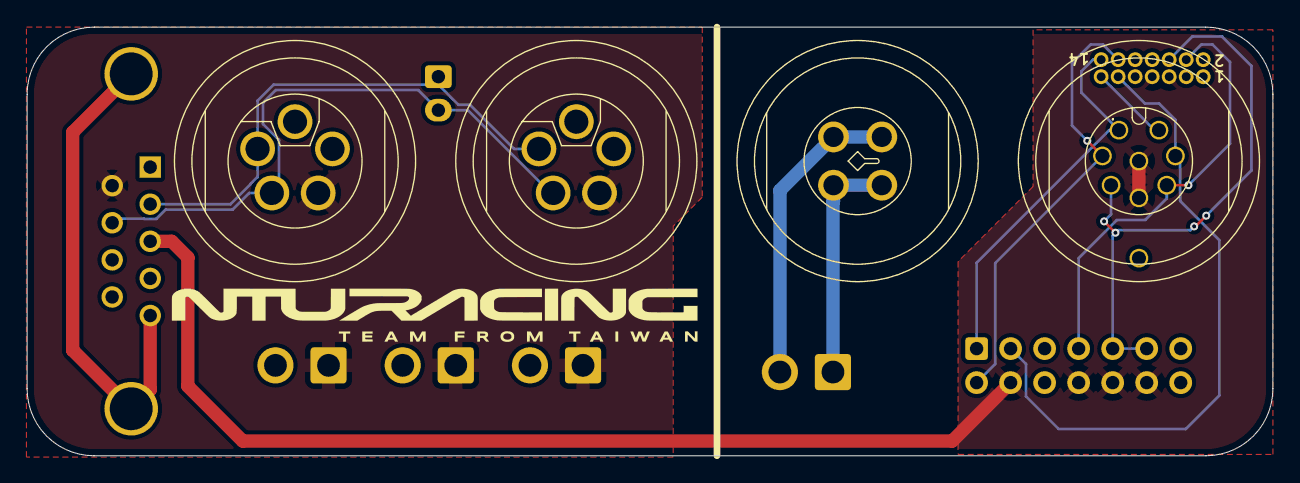
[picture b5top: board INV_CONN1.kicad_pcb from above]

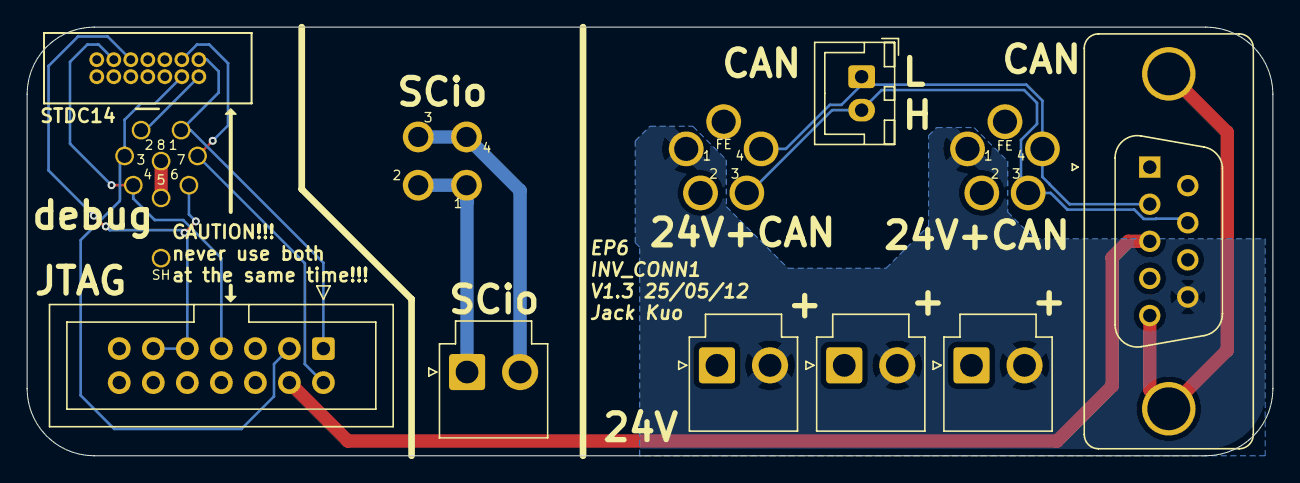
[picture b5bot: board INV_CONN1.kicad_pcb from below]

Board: 2 copper layers, 93.0 x 32.0 mm, 12 parts (8 on the bottom side), 14 nets.

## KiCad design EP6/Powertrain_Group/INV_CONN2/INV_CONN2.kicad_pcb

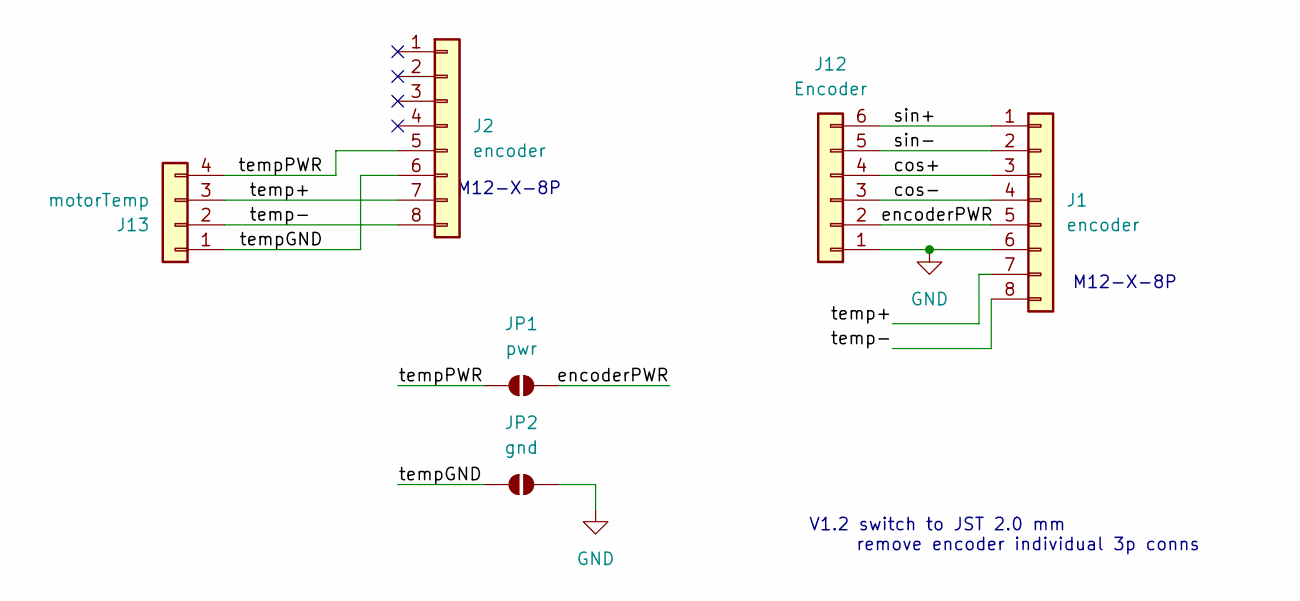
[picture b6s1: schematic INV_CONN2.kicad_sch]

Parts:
J1, J2: encoder; NianYeong-M12-X-F4P
J12: Encoder; JST_PH_B6B-PH-K_1x06_P2.00mm_Vertical
J13: motorTemp; JST_PH_B4B-PH-K_1x04_P2.00mm_Vertical
JP1: pwr; SolderJumper-2_P1.3mm_Open_RoundedPad1.0x1.5mm
JP2: gnd; SolderJumper-2_P1.3mm_Open_RoundedPad1.0x1.5mm

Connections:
/cos+: J1.3, J12.4
/cos-: J1.4, J12.3
/encoderPWR: J1.5, J12.2, JP1.2 (B)
/sin+: J1.1, J12.6
/sin-: J1.2, J12.5
/temp+: J1.7, J2.7, J13.3
/temp-: J1.8, J2.8, J13.2
/tempGND: J2.6, J13.1, JP2.1 (A)
/tempPWR: J2.5, J13.4, JP1.1 (A)
GND: J1.6, J12.1, JP2.2 (B)

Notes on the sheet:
M12-X-8P
V1.2 switch to JST 2.0 mm remove encoder individual 3p conns

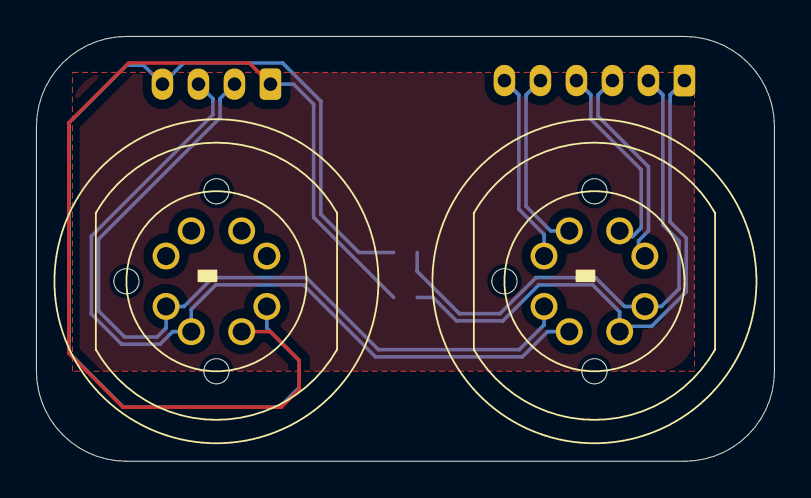
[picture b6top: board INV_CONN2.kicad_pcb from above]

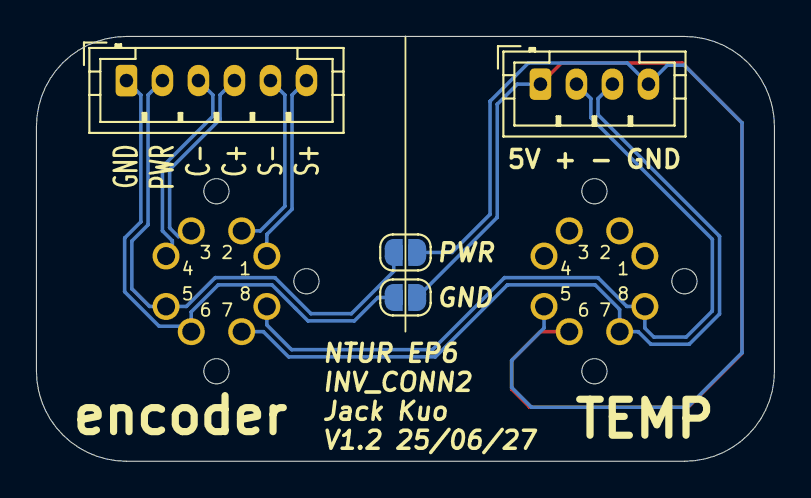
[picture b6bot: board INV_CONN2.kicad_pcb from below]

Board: 2 copper layers, 41.0 x 23.6 mm, 6 parts (4 on the bottom side), 10 nets.
